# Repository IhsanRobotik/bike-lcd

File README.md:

<div align="center">

# E-bike Battery & Speed Meter

**A custom LCD readout for a common Chinese e-bike controller.**  
Battery voltage and wheel speed, on a small STM32-powered display.

*Custom display and controller board — designed in KiCad.*

</div>

---

## The project

A personal hardware project to add a dedicated battery and speed readout to a familiar e-bike setup. The design pairs a **16×2 character LCD** with an **STM32F103C6** microcontroller. The schematic includes a battery-voltage input and a `TACHO` speed signal.

## A closer look

<table>
  <tr>
    <td width="50%" align="center"><br><sub>Custom controller PCB</sub></td>
    <td width="50%" align="center"><br><sub>Display and board assembly</sub></td>
  </tr>
</table>

### Schematic & PCB layout

<table>
  <tr>
    <td width="50%" align="center"><br><sub>STM32, LCD, battery-voltage sense, and TACHO input</sub></td>
    <td width="50%" align="center"><br><sub>Routed PCB layout</sub></td>
  </tr>
</table>

### At a glance

| | |
|---|---|
| Display | WC1602A, 16×2 character LCD |
| Microcontroller | STM32F103C6 |
| Speed input | `TACHO` signal |
| Battery input | Battery-voltage sense |
| Design tools | KiCad |

## Design files

- [Schematic (PDF)](exports/schematic.pdf)
- [PCB layout (PDF)](exports/board.pdf)
- [3D assembly model (STEP)](exports/bike%20lcd.step)
- [Gerber copper layer](gerber/bike%20lcd-F_Cu.gbr)

The KiCad schematic and board files are also in the repository.

## PCB milling

The repository also includes CNC toolpaths for milling the board, drilling the holes, and cutting the outline. The image shows a simulation of the front copper toolpath.

<p align="center">
  <br>
  <sub>Simulated front-copper milling toolpath</sub>
</p>

- [Front copper toolpath (G-code)](gcode/front.nc)
- [Drilling toolpath (G-code)](gcode/drill.nc)
- [Board outline toolpath (G-code)](gcode/outline.nc)
- [All CNC and toolpath files](gcode/)

These files are machine-specific outputs; check the setup and tool settings before running them on a CNC mill.

---

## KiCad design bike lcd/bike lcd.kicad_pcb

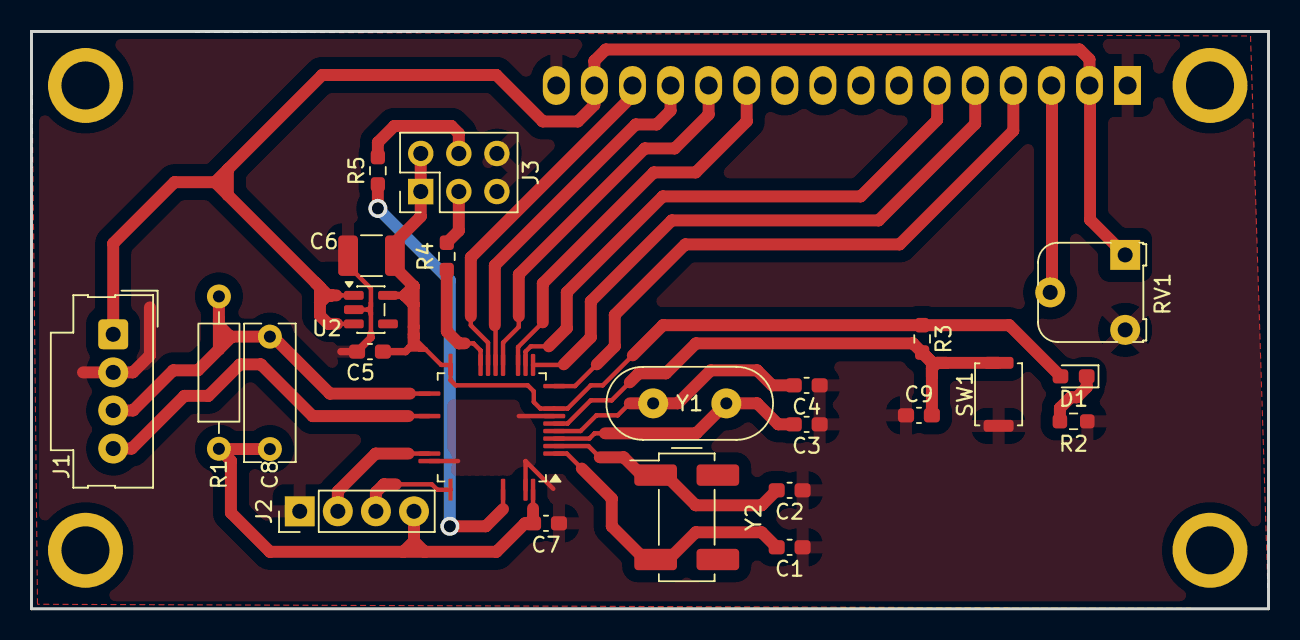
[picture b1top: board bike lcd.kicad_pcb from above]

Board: 2 copper layers, 82.5 x 38.5 mm, 25 parts (1 on the bottom side), 25 nets.

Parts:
C1, C2: 20pf; C_0603_1608Metric_Pad1.08x0.95mm_HandSolder
C3, C4, C9: 10pf; C_0603_1608Metric_Pad1.08x0.95mm_HandSolder
C5, C7: 100nf; C_0603_1608Metric_Pad1.08x0.95mm_HandSolder
C6: 100uf; C_1210_3225Metric_Pad1.33x2.70mm_HandSolder
C8: C; C_Rect_L9.0mm_W3.2mm_P7.50mm_MKT
D1: LED; LED_0603_1608Metric_Pad1.05x0.95mm_HandSolder
DS1: WC1602A
J1: MOLEX; Molex_SL_171971-0004_1x04_P2.54mm_Vertical
J2: PROGRAMMER; PinHeader_1x04_P2.54mm_Vertical
J3: Conn_02x03_Odd_Even; PinHeader_2x03_P2.54mm_Vertical
R1: 4.7k; R_Axial_DIN0207_L6.3mm_D2.5mm_P10.16mm_Horizontal
R2, R3, R4, R5: R; R_0603_1608Metric_Pad0.98x0.95mm_HandSolder
RV1: R_Potentiometer; Potentiometer_Runtron_RM-065_Vertical
SW1: SW_Push; SW_Push_SPST_NO_Alps_SKRK
U1: STM32F103C6Tx; LQFP-48_7x7mm_P0.5mm
U2: AP2112K-3.3; SOT-23-5
Y1: 32k; Crystal_HC49-U_Vertical
Y2: 8Mhz; Crystal_SMD_SeikoEpson_MC306-4Pin_8.0x3.2mm_HandSoldering

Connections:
+5V: DS1.2 (VDD), DS1.15 (LED(+)), J1.1, RV1.1, U2.1 (VIN), U2.3 (EN)
BATTERY VOLTAGE: J1.4, U1.29 (PA8)
BD 4: DS1.11 (D4), U1.15 (PA5)
BD 5: DS1.12 (D5), U1.17 (PA7)
BD 6: DS1.13 (D6), U1.18 (PB0)
BD 7: DS1.14 (D7), U1.19 (PB1)
BOOT0: R5.1, U1.44 (BOOT0)
BOOT1: R4.1, U1.20 (PB2)
E: DS1.6 (E), U1.14 (PA4)
GND: C1.1, C2.1, C3.1, C4.1, C5.1, C6.2, C7.1, C9.2, DS1.1 (VSS), DS1.16 (LED(-)), J1.2, J2.1, J3.5, J3.6, R2.2, RV1.3, SW1.1, U1.8 (VSSA), U1.35 (VSS), U1.47 (VSS), U2.2 (GND)
unnamed: D1.1 (K), R2.1
unnamed: DS1.3 (VO), RV1.2
unnamed: J2.2, U1.34 (PA13)
unnamed: J2.3, U1.37 (PA14)
unnamed: J3.3, R4.2
unnamed: J3.4, R5.2
unnamed: C1.2, U1.3 (PC14), Y2.2
unnamed: C2.2, U1.4 (PC15), Y2.1
unnamed: C3.2, U1.5 (PD0), Y1.1
unnamed: C4.2, U1.6 (PD1), Y1.2
RS: DS1.4 (RS), U1.12 (PA2)
RST: C9.1, R3.2, SW1.2, U1.7 (NRST)
R/W: DS1.5 (R/W), U1.13 (PA3)
TACHO: C8.2, J1.3, R1.2, U1.26 (PB13)
VDD: C5.2, C6.1, C7.2, C8.1, D1.2 (A), J2.4, J3.1, J3.2, R1.1, R3.1, U1.9 (VDDA), U1.24 (VDD), U1.48 (VDD), U2.5 (VOUT)
